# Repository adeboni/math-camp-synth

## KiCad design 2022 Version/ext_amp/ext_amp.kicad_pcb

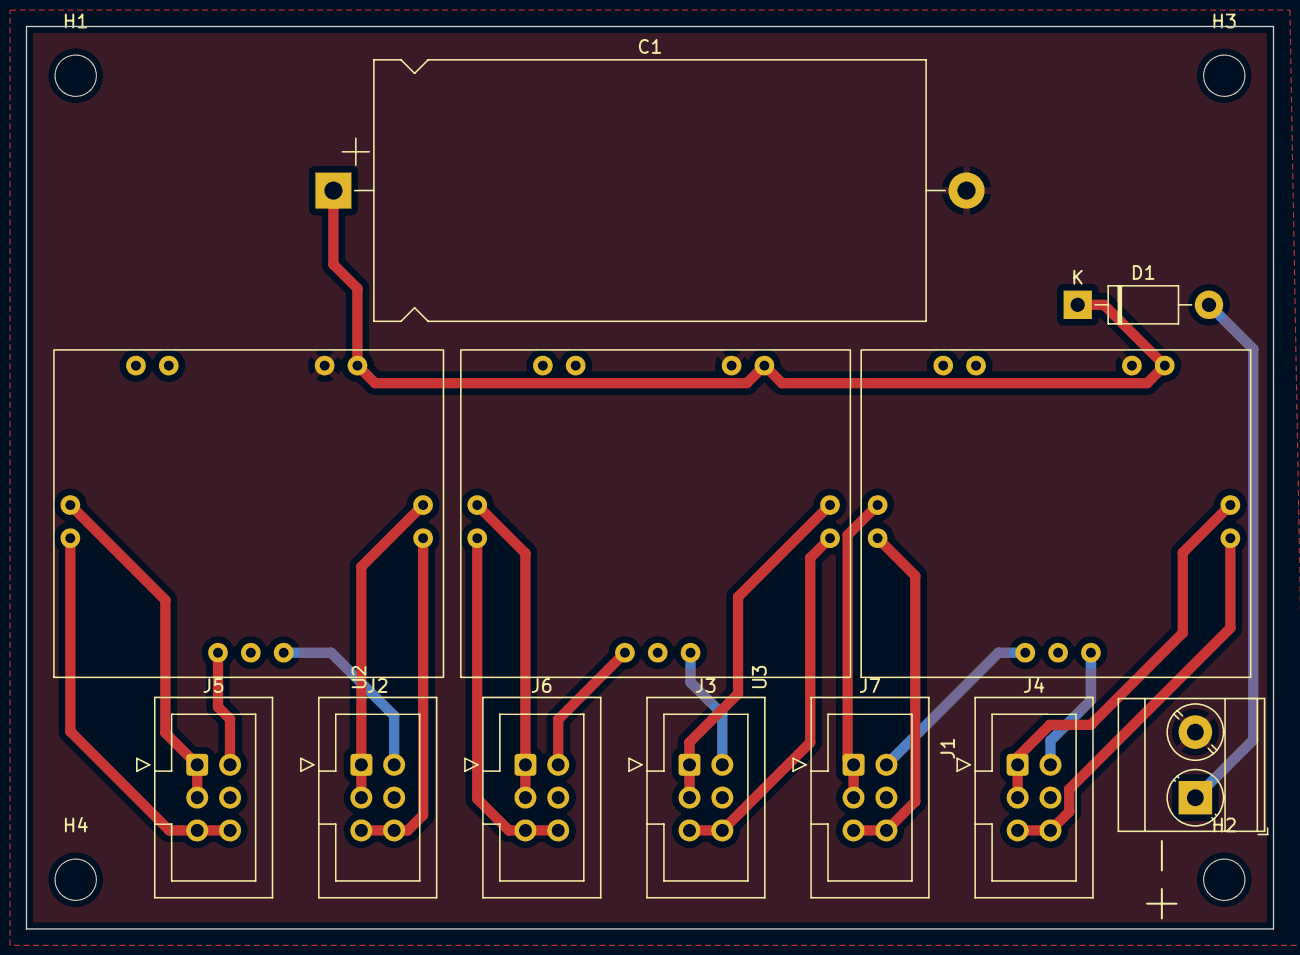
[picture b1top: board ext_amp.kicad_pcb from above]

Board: 2 copper layers, 96.5 x 69.9 mm, 16 parts (0 on the bottom side), 22 nets.

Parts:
C1: 4700u; CP_Axial_L42.5mm_D20.0mm_P49.00mm_Horizontal
D1: 1N4007; D_DO-41_SOD81_P10.16mm_Horizontal
H1, H2, H3, H4: MountingHole; MountingHole_3.2mm_M3
J1: Screw_Terminal_01x02; TerminalBlock_Phoenix_MKDS-3-2-5.08_1x02_P5.08mm_Horizontal
J2, J3, J4, J5, J6, J7: Conn_02x03_Odd_Even; IDC-Header_2x03_P2.54mm_Vertical
U1, U2, U3: PAM8610_Module

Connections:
+12V: C1.1, D1.1 (K), U1.2 (PWR_12V), U2.2 (PWR_12V), U3.2 (PWR_12V)
GND: C1.2, J1.2, U1.1 (PWR_GND), U2.1 (PWR_GND), U3.1 (PWR_GND)
IN1+: J2.2, U1.7 (L_IN)
IN2+: J5.2, U1.5 (R_IN)
IN3+: J3.2, U2.7 (L_IN)
IN4+: J6.2, U2.5 (R_IN)
IN5+: J4.2, U3.7 (L_IN)
IN6+: J7.2, U3.5 (R_IN)
IN-: J2.4, J3.4, J4.4, J5.4, J6.4, J7.4, U1.6 (GND_IN), U2.6 (GND_IN), U3.6 (GND_IN)
unnamed: D1.2 (A), J1.1
OUT1+: J2.1, J2.3, U1.11 (L+)
OUT1-: J2.5, J2.6, U1.10 (L-)
OUT2+: J5.1, J5.3, U1.9 (R+)
OUT2-: J5.5, J5.6, U1.8 (R-)
OUT3+: J3.1, J3.3, U2.11 (L+)
OUT3-: J3.5, J3.6, U2.10 (L-)
OUT4+: J6.1, J6.3, U2.9 (R+)
OUT4-: J6.5, J6.6, U2.8 (R-)
OUT5+: J4.1, J4.3, U3.11 (L+)
OUT5-: J4.5, J4.6, U3.10 (L-)
OUT6+: J7.1, J7.3, U3.9 (R+)
OUT6-: J7.5, J7.6, U3.8 (R-)

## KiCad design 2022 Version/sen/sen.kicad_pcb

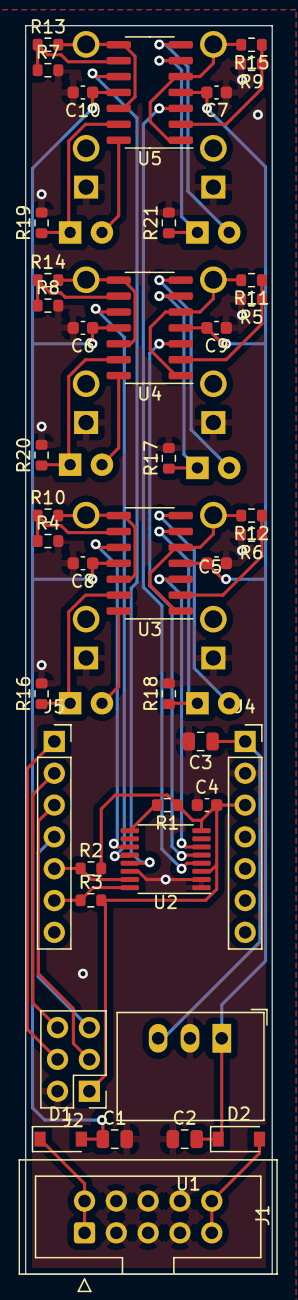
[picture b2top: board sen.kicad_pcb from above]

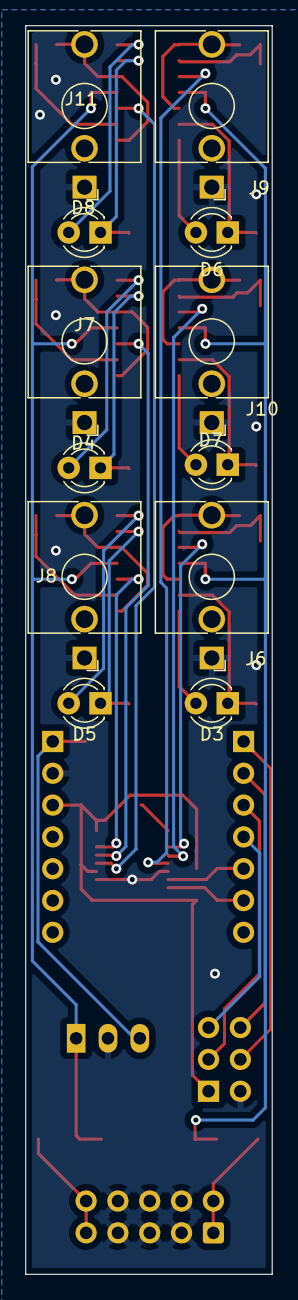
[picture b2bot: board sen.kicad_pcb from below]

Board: 2 copper layers, 19.7 x 99.7 mm, 54 parts (12 on the bottom side), 44 nets.

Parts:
C1, C2, C3: 22u; C_0805_2012Metric
C4, C5, C6, C7, C8, C9, C10: 100n; C_0603_1608Metric
D1, D2: 1N5819; D_SOD-123
D3, D4, D5, D6, D7, D8: LED; LED_D3.0mm_FlatTop
J1: Conn_02x05_Odd_Even; IDC-Header_2x05_P2.54mm_Vertical
J2: Conn_02x03_Odd_Even; PinHeader_2x03_P2.54mm_Vertical
J4, J5: Conn_01x07; PinSocket_1x07_P2.54mm_Vertical
J6, J7, J8, J9, J10, J11: AudioJack2_SwitchT; Jack_3.5mm_QingPu_WQP-PJ398SM_Vertical_CircularHoles
R1, R2, R3, R10, R11, R12, R13, R14, R15: 10k; R_0603_1608Metric
R4, R5, R6, R7, R8, R9: 4.7k; R_0603_1608Metric
R16, R17, R18, R19, R20, R21: 1k; R_0603_1608Metric
U1: R-78C3.3-1.0; Converter_DCDC_RECOM_R-78E-0.5_THT
U2: DAC7578xPW; TSSOP-16_4.4x5mm_P0.65mm
U3, U4, U5: TL074; SOIC-14_3.9x8.7mm_P1.27mm

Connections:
+3V3: C4.2, J2.1, J4.3, R1.1, R2.2, R3.2, U2.3 (AVDD), U2.8 (VREFIN)
+5V: C3.1, J4.1, U1.3 (OUT)
+12V: C2.2, C5.2, C7.2, C9.2, D2.1 (K), U1.1 (IN), U3.4 (V+), U4.4 (V+), U5.4 (V+)
-12V: C1.1, C6.1, C8.1, C10.1, D1.2 (A), U3.11 (V-), U4.11 (V-), U5.11 (V-)
A0: J2.4, J5.1
A1: J2.6, J5.2
A2: J2.3, J5.3
A3: J2.5, J5.4
GND: C1.2, C2.1, C3.2, C4.1, C5.1, C6.2, C7.1, C8.2, C9.1, C10.2, J1.3, J1.4, J1.5, J1.6, J1.7, J1.8, J2.2, J4.2, J6.S, J7.S, J8.S, J9.S, J10.S, J11.S, R4.2, R5.2, R6.2, R7.2, R8.2, R9.2, R16.2, R17.2, R18.2, R19.2, R20.2, R21.2, U1.2 (GND), U2.1 (~LDAC), U2.2 (ADDR0), U2.14 (GND)
unnamed: D1.1 (K), J1.1, J1.2
unnamed: D2.2 (A), J1.9, J1.10
unnamed: D3.1 (K), R16.1, U3.13 (-)
unnamed: D3.2 (A), U3.14
unnamed: D4.1 (K), R17.1, U4.6 (-)
unnamed: D4.2 (A), U4.7
unnamed: D5.1 (K), R18.1, U3.6 (-)
unnamed: D5.2 (A), U3.7
unnamed: D6.1 (K), R19.1, U5.13 (-)
unnamed: D6.2 (A), U5.14
unnamed: D7.1 (K), R20.1, U4.13 (-)
unnamed: D7.2 (A), U4.14
unnamed: D8.1 (K), R21.1, U5.6 (-)
unnamed: D8.2 (A), U5.7
unnamed: J6.T, R10.2, U3.8, U3.12 (+)
unnamed: J7.T, R11.2, U4.1, U4.5 (+)
unnamed: J8.T, R12.2, U3.1, U3.5 (+)
unnamed: J9.T, R13.2, U5.8, U5.12 (+)
unnamed: J10.T, R14.2, U4.8, U4.12 (+)
unnamed: J11.T, R15.2, U5.1, U5.5 (+)
unnamed: R1.2, U2.9 (~CLR)
unnamed: R4.1, R10.1, U3.9 (-)
unnamed: R5.1, R11.1, U4.2 (-)
unnamed: R6.1, R12.1, U3.2 (-)
unnamed: R7.1, R13.1, U5.9 (-)
unnamed: R8.1, R14.1, U4.9 (-)
unnamed: R9.1, R15.1, U5.2 (-)
unnamed: U2.4 (VOUTA), U5.3 (+)
unnamed: U2.5 (VOUTC), U4.3 (+)
unnamed: U2.6 (VOUTE), U3.3 (+)
unnamed: U2.11 (VOUTF), U3.10 (+)
unnamed: U2.12 (VOUTD), U4.10 (+)
unnamed: U2.13 (VOUTB), U5.10 (+)
SCL: J5.6, R3.1, U2.16 (SCL)
SDA: J5.5, R2.1, U2.15 (SDA)

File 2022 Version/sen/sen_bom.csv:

Comment,Designator,Footprint,LCSC Part Number
100n,"C7,C5,C10,C4,C6,C8,C9",C_0603_1608Metric,C14663
1k,"R19,R18,R20,R16,R17,R21",R_0603_1608Metric,C21190
10k,"R15,R3,R13,R11,R2,R12,R1,R14,R10",R_0603_1608Metric,C25804
22u,"C2,C1,C3",C_0805_2012Metric,C129303
TL074,"U4,U3,U5",SOIC-14_3.9x8.7mm_P1.27mm,C6963
DAC7578xPW,U2,TSSOP-16_4.4x5mm_P0.65mm,C1520855
4.7k,"R4,R7,R9,R6,R8,R5",R_0603_1608Metric,C23162
1N5819,"D1,D2",D_SOD-123,C963381

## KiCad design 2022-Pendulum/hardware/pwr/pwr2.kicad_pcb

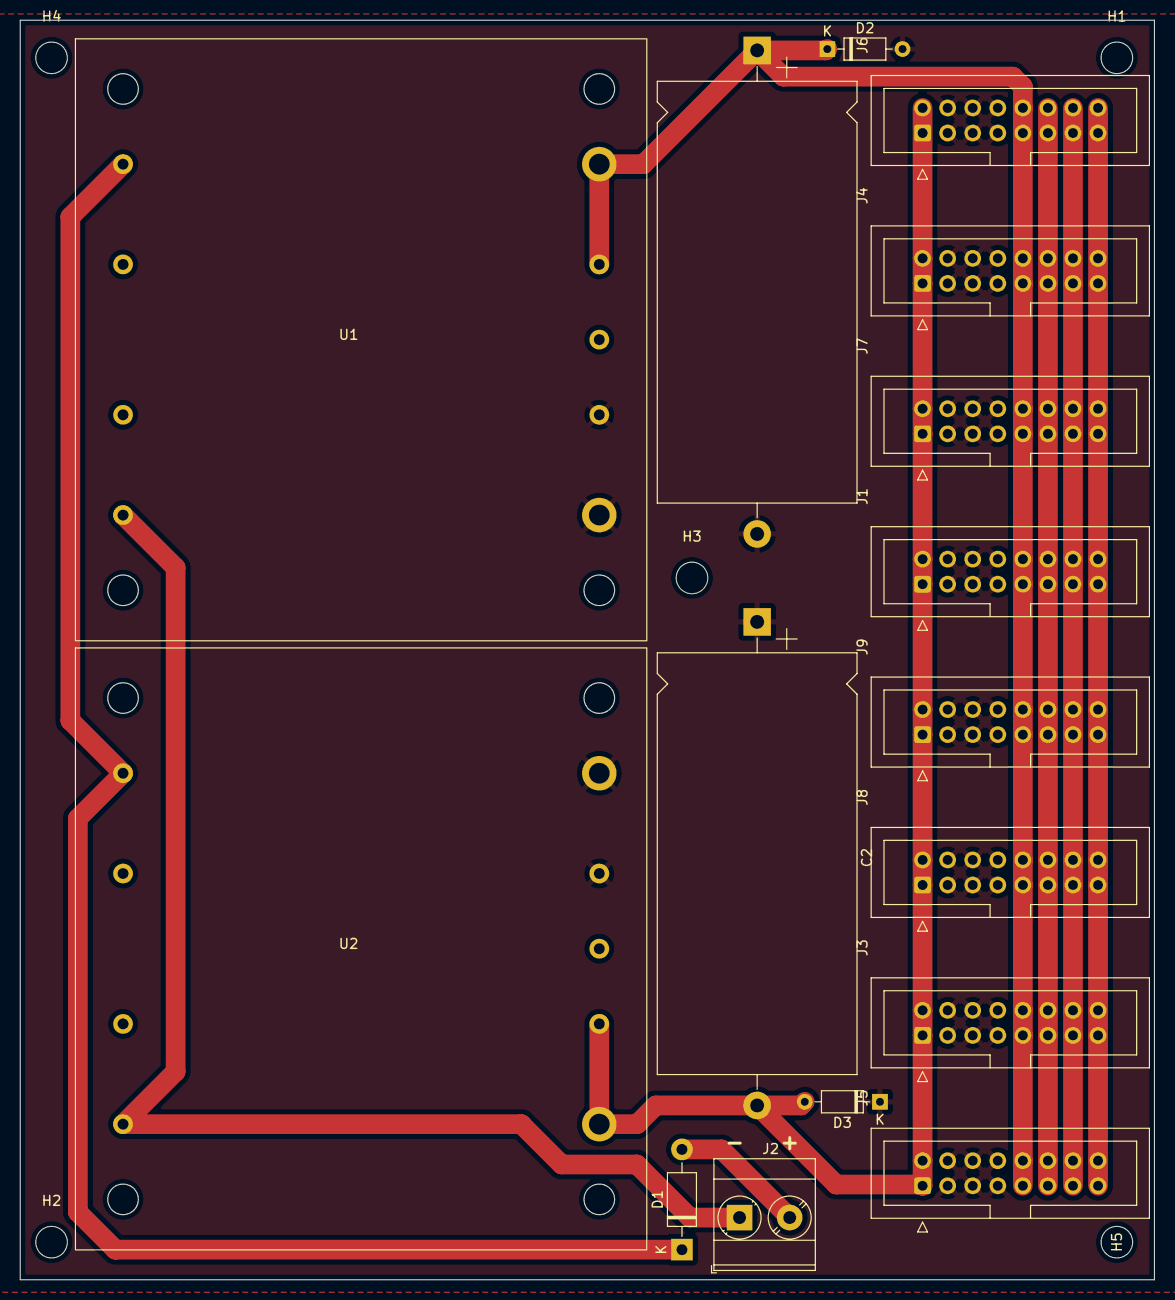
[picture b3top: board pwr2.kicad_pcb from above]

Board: 2 copper layers, 114.9 x 127.6 mm, 21 parts (0 on the bottom side), 9 nets.

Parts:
C1, C2: 4700u; CP_Axial_L42.5mm_D20.0mm_P49.00mm_Horizontal
D1: 1N4007; D_DO-41_SOD81_P10.16mm_Horizontal
D2, D3: 1N4148; D_DO-35_SOD27_P7.62mm_Horizontal
H1, H2, H3, H4, H5: MountingHole; MountingHole_3.2mm_M3
J1, J3, J4, J5, J6, J7, J8, J9: Conn_02x08_Odd_Even; IDC-Header_2x08_P2.54mm_Vertical
J2: Screw_Terminal_01x02; TerminalBlock_Phoenix_MKDS-3-2-5.08_1x02_P5.08mm_Horizontal
U1, U2: VHB75

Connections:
+12V: C1.1, D2.1 (K), J1.9, J1.10, J3.9, J3.10, J4.9, J4.10, J5.9, J5.10, J6.9, J6.10, J7.9, J7.10, J8.9, J8.10, J9.9, J9.10, U1.8 (+Sense), U1.9 (+Vout)
-12V: C2.2, D3.2 (A), J1.1, J1.2, J3.1, J3.2, J4.1, J4.2, J5.1, J5.2, J6.1, J6.2, J7.1, J7.2, J8.1, J8.2, J9.1, J9.2, U2.5 (-Vout), U2.6 (-Sense)
GND: C1.2, C2.1, D2.2 (A), D3.1 (K), J1.3, J1.4, J1.5, J1.6, J1.7, J1.8, J3.3, J3.4, J3.5, J3.6, J3.7, J3.8, J4.3, J4.4, J4.5, J4.6, J4.7, J4.8, J5.3, J5.4, J5.5, J5.6, J5.7, J5.8, J6.3, J6.4, J6.5, J6.6, J6.7, J6.8, J7.3, J7.4, J7.5, J7.6, J7.7, J7.8, J8.3, J8.4, J8.5, J8.6, J8.7, J8.8, J9.3, J9.4, J9.5, J9.6, J9.7, J9.8, U1.5 (-Vout), U1.6 (-Sense), U2.8 (+Sense), U2.9 (+Vout)
unnamed: D1.1 (K), U1.1 (+Vin), U2.1 (+Vin)
unnamed: D1.2 (A), J2.2
unnamed: J1.11, J1.12, J3.11, J3.12, J4.11, J4.12, J5.11, J5.12, J6.11, J6.12, J7.11, J7.12, J8.11, J8.12, J9.11, J9.12
unnamed: J1.13, J1.14, J3.13, J3.14, J4.13, J4.14, J5.13, J5.14, J6.13, J6.14, J7.13, J7.14, J8.13, J8.14, J9.13, J9.14
unnamed: J1.15, J1.16, J3.15, J3.16, J4.15, J4.16, J5.15, J5.16, J6.15, J6.16, J7.15, J7.16, J8.15, J8.16, J9.15, J9.16
unnamed: J2.1, U1.4 (-Vin), U2.4 (-Vin)

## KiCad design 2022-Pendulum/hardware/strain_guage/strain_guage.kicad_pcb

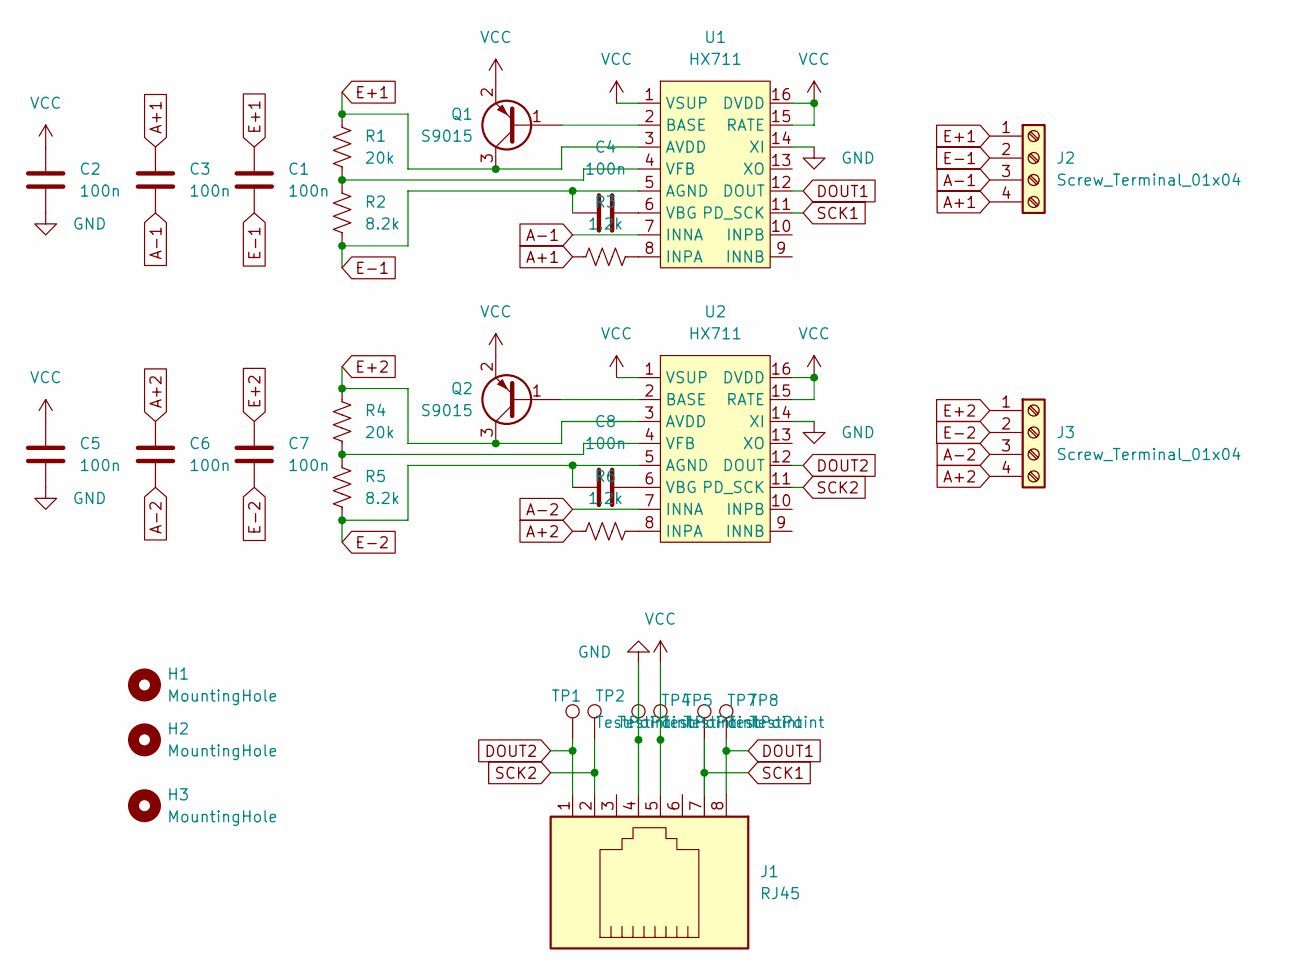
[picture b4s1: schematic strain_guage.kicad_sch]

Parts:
C1, C2, C3, C4, C5, C6, C7, C8: 100n; C_0603_1608Metric
H1, H2, H3: MountingHole; MountingHole_3.2mm_M3
J1: RJ45; RJ45_OST_PJ012-8P8CX_Vertical
J2, J3: Screw_Terminal_01x04; TerminalBlock_bornier-4_P5.08mm
Q1, Q2: S9015; SOT-23
R1, R4: 20k; R_0603_1608Metric
R2, R5: 8.2k; R_0603_1608Metric
R3, R6: 1.2k; R_0603_1608Metric
TP1, TP2, TP4, TP5, TP7, TP8: TestPoint; TestPoint_WireHole
U1, U2: HX711; SOIC-16_3.9x9.9mm_P1.27mm

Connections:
A+1: C3.1, J2.4, R3.1
A+2: C6.1, J3.4, R6.1
A-1: C3.2, J2.3, U1.7 (INNA)
A-2: C6.2, J3.3, U2.7 (INNA)
DOUT1: J1.8, TP8.1, U1.12 (DOUT)
DOUT2: J1.1, TP1.1, U2.12 (DOUT)
E+1: C1.1, J2.1, Q1.3 (C), R1.1, U1.3 (AVDD)
E+2: C7.1, J3.1, Q2.3 (C), R4.1, U2.3 (AVDD)
E-1: C1.2, C4.1, J2.2, R2.2, U1.5 (AGND)
E-2: C7.2, C8.1, J3.2, R5.2, U2.5 (AGND)
GND: C2.2, C5.2, J1.4, TP4.1, U1.14 (XI), U2.14 (XI)
unnamed: C8.2, U2.6 (VBG)
unnamed: Q2.1 (B), U2.2 (BASE)
unnamed: R4.2, R5.1, U2.4 (VFB)
unnamed: R6.2, U2.8 (INPA)
unnamed: Q1.1 (B), U1.2 (BASE)
unnamed: R1.2, R2.1, U1.4 (VFB)
unnamed: C4.2, U1.6 (VBG)
unnamed: R3.2, U1.8 (INPA)
SCK1: J1.7, TP7.1, U1.11 (PD_SCK)
SCK2: J1.2, TP2.1, U2.11 (PD_SCK)
VCC: C2.1, C5.1, J1.5, Q1.2 (E), Q2.2 (E), TP5.1, U1.1 (VSUP), U1.15 (RATE), U1.16 (DVDD), U2.1 (VSUP), U2.15 (RATE), U2.16 (DVDD)

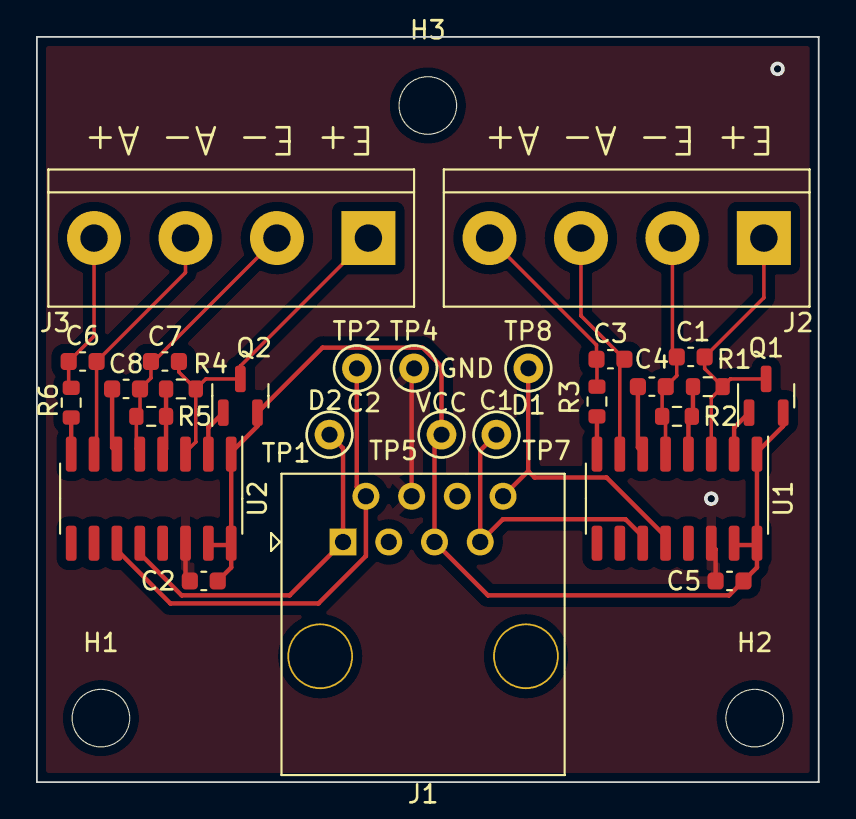
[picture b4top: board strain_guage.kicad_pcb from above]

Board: 2 copper layers, 43.4 x 41.4 mm, 30 parts (0 on the bottom side), 22 nets.

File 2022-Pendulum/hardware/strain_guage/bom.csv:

Comment,Designator,Footprint,LCSC Part Number
HX711,"U2,U1",SOIC-16_3.9x9.9mm_P1.27mm,C43656
100n,"C5,C2,C6,C1,C3,C8,C7,C4",C_0603_1608Metric,C14663
1.2k,"R6,R3",R_0603_1608Metric,C22765
8.2k,"R5,R2",R_0603_1608Metric,C25981
S9015,"Q1,Q2",SOT-23,C2149
20k,"R1,R4",R_0603_1608Metric,C4184

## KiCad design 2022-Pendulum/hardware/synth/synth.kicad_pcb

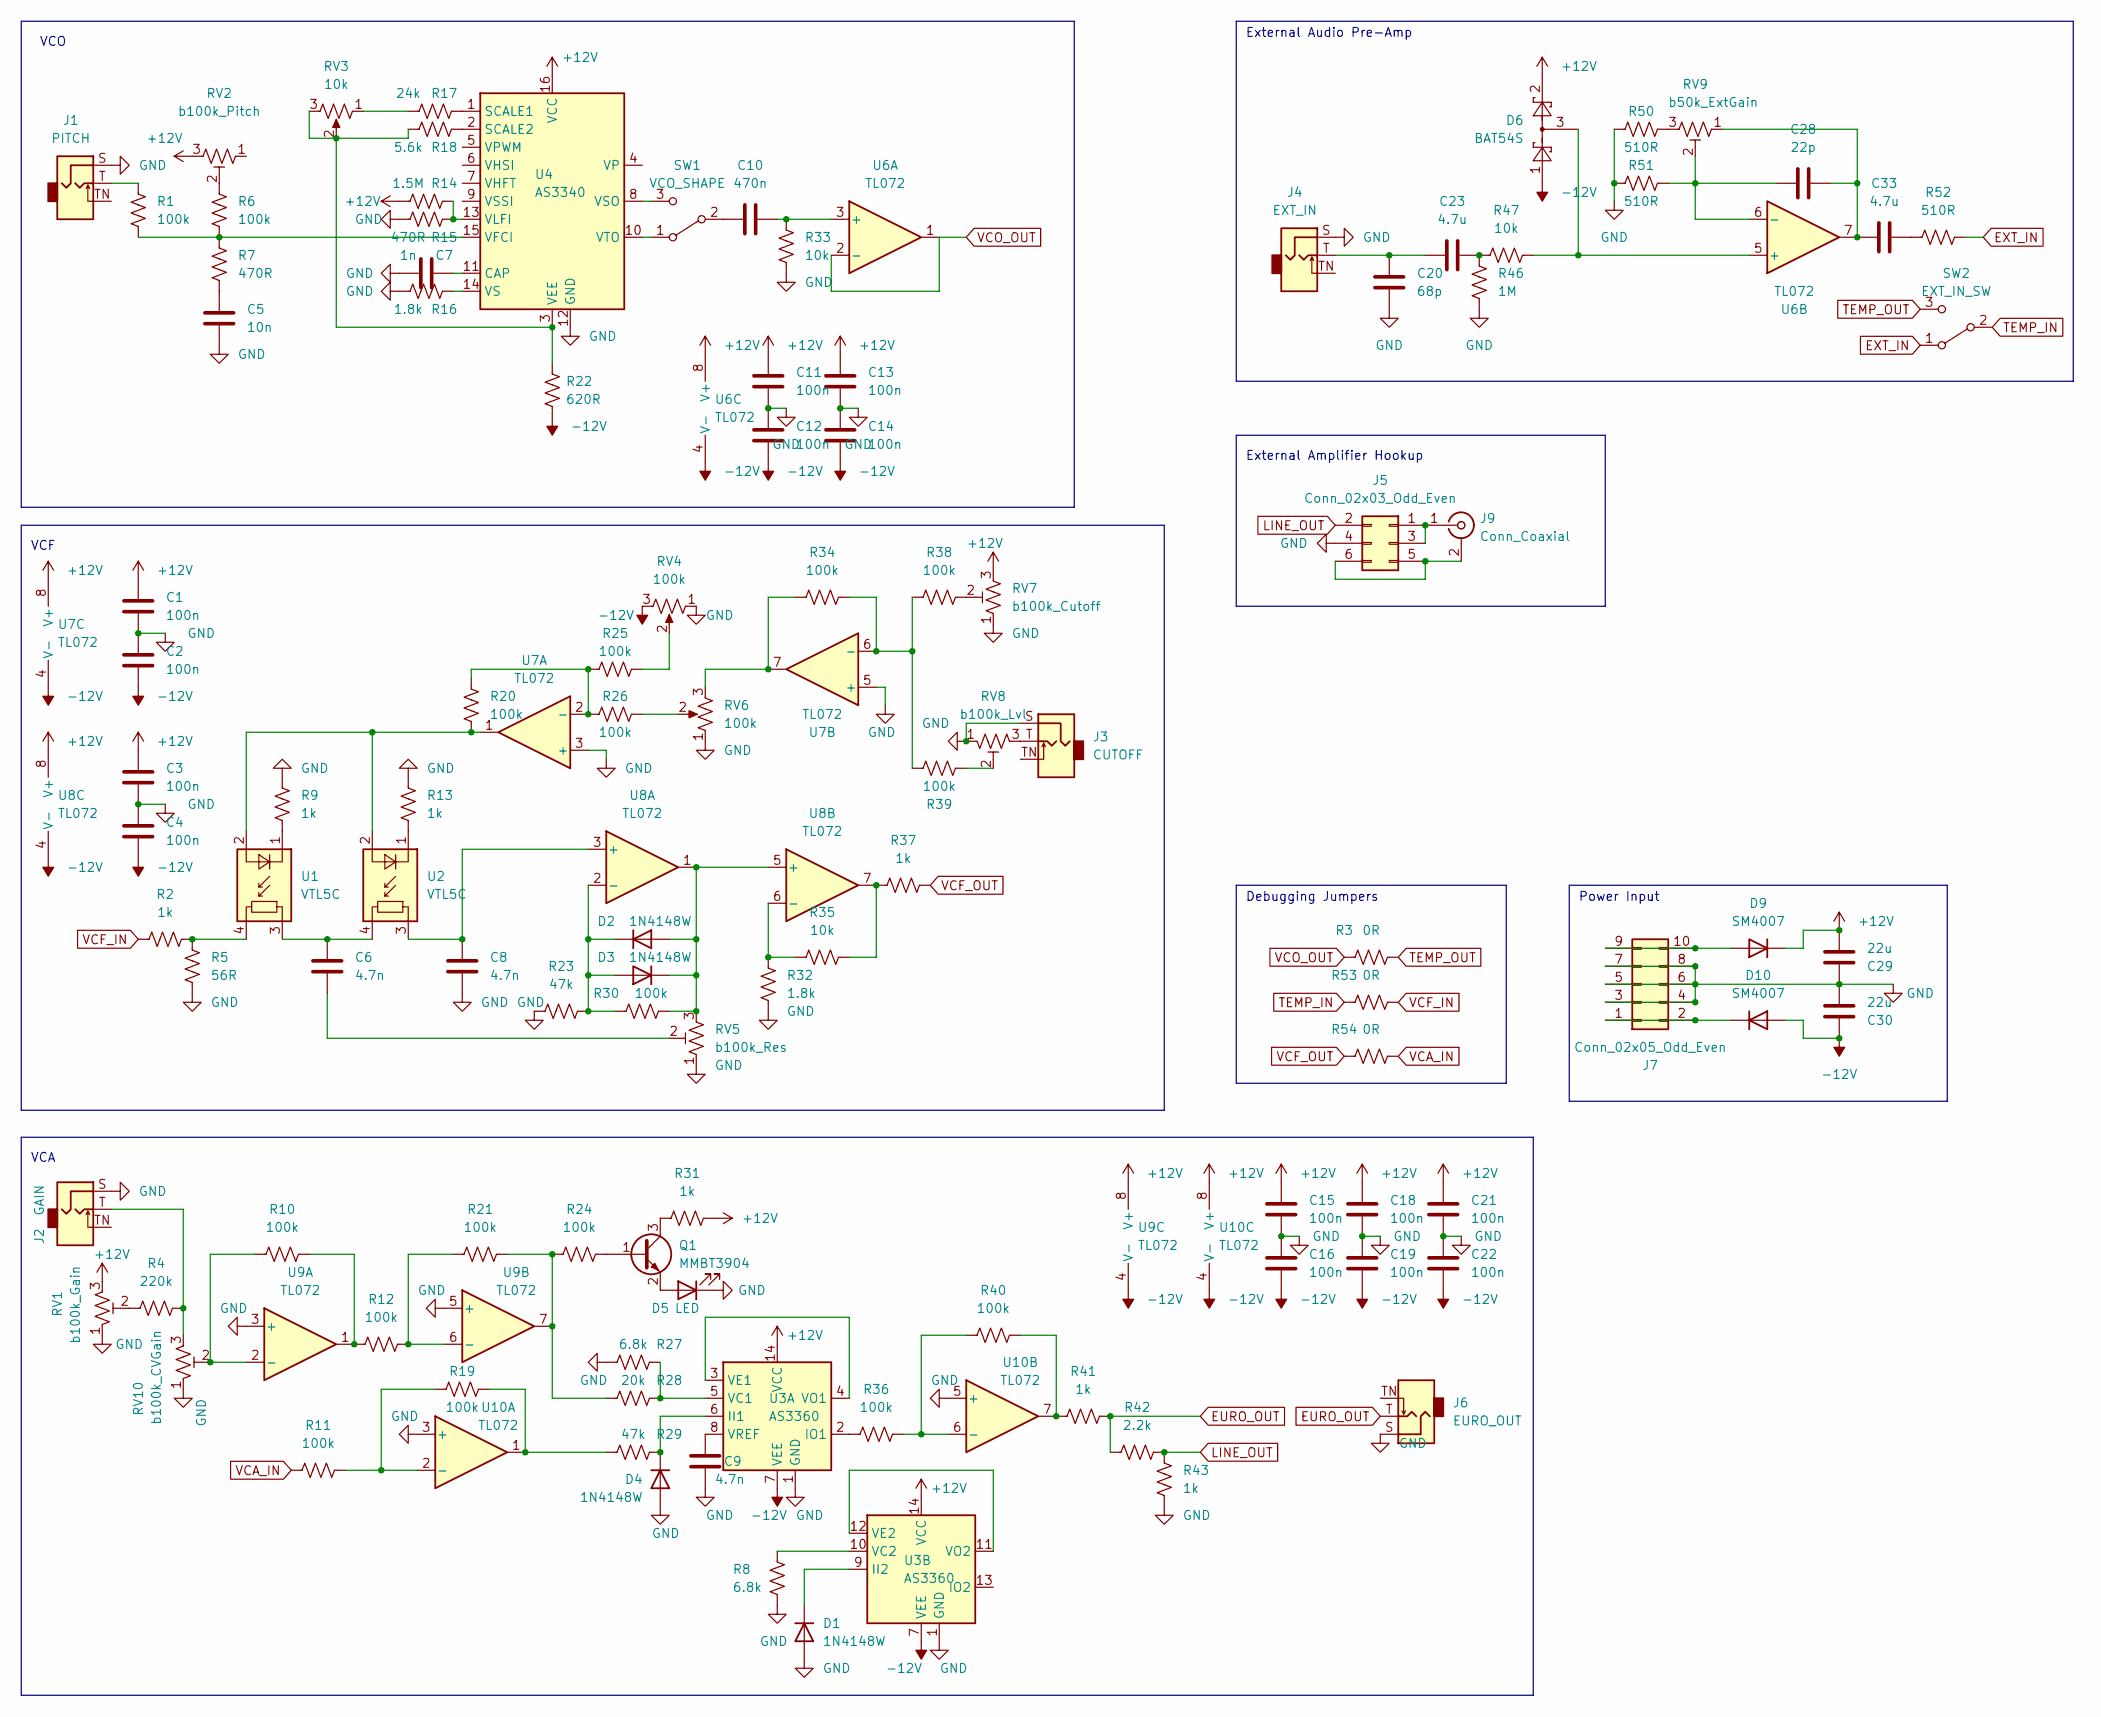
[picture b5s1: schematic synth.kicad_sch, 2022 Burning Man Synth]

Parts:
C1, C2, C3, C4, C11, C12, C13, C14, C15, C16, C18, C19, C21, C22: 100n; C_0603_1608Metric
C5: 10n; C_0603_1608Metric
C6, C8, C9: 4.7n; C_0603_1608Metric
C7: 1n; C_0603_1608Metric
C10: 470n; C_0603_1608Metric
C20: 68p; C_0603_1608Metric
C23, C33: 4.7u; C_0603_1608Metric
C28: 22p; C_0603_1608Metric
C29, C30: 22u; C_0805_2012Metric
D1, D2, D3, D4: 1N4148W; D_SOD-123
D5: LED; LED_D3.0mm
D6: BAT54S; SOT-23
D9, D10: SM4007; D_SOD-123
J1: PITCH; Jack_3.5mm_QingPu_WQP-PJ398SM_Vertical_CircularHoles
J2: GAIN; Jack_3.5mm_QingPu_WQP-PJ398SM_Vertical_CircularHoles
J3: CUTOFF; Jack_3.5mm_QingPu_WQP-PJ398SM_Vertical_CircularHoles
J4: EXT_IN; Jack_3.5mm_QingPu_WQP-PJ398SM_Vertical_CircularHoles
J5: Conn_02x03_Odd_Even; IDC-Header_2x03_P2.54mm_Vertical
J6: EURO_OUT; Jack_3.5mm_QingPu_WQP-PJ398SM_Vertical_CircularHoles
J7: Conn_02x05_Odd_Even; IDC-Header_2x05_P2.54mm_Vertical
J9: Conn_Coaxial; RCA
Q1: MMBT3904; SOT-23
R1, R6, R10, R11, R12, R19, R20, R21, R24, R25, R26, R30, R34, R36, R38, R39, R40: 100k; R_0603_1608Metric
R2, R9, R13, R31, R37, R41, R43: 1k; R_0603_1608Metric
R3, R53, R54: 0R; R_0603_1608Metric
R4: 220k; R_0603_1608Metric
R5: 56R; R_0603_1608Metric
R7, R15: 470R; R_0603_1608Metric
R8, R27: 6.8k; R_0603_1608Metric
R14: 1.5M; R_0603_1608Metric
R16, R32: 1.8k; R_0603_1608Metric
R17: 24k; R_0603_1608Metric
R18: 5.6k; R_0603_1608Metric
R22: 620R; R_0603_1608Metric
R23, R29: 47k; R_0603_1608Metric
R28: 20k; R_0603_1608Metric
R33, R35, R47: 10k; R_0603_1608Metric
R42: 2.2k; R_0603_1608Metric
R46: 1M; R_0603_1608Metric
R50, R51, R52: 510R; R_0603_1608Metric
RV1: b100k_Gain; Potentiometer_Alpha_RD901F-40-00D_Single_Vertical
RV2: b100k_Pitch; Potentiometer_Alpha_RD901F-40-00D_Single_Vertical
RV3: 10k; Potentiometer_Bourns_3314G_Vertical
RV4, RV6: 100k; Potentiometer_Bourns_3314G_Vertical
RV5: b100k_Res; Potentiometer_Alpha_RD901F-40-00D_Single_Vertical
RV7: b100k_Cutoff; Potentiometer_Alpha_RD901F-40-00D_Single_Vertical
RV8: b100k_Lvl; Potentiometer_Alpha_RD901F-40-00D_Single_Vertical
RV9: b50k_ExtGain; Potentiometer_Alpha_RD901F-40-00D_Single_Vertical
RV10: b100k_CVGain; Potentiometer_Alpha_RD901F-40-00D_Single_Vertical
SW1: VCO_SHAPE; Switch_Toggle_SPDT_Mini_SolderLug
SW2: EXT_IN_SW; Switch_Toggle_SPDT_Mini_SolderLug
U1, U2: VTL5C; PerkinElmer_VTL5C
U3: AS3360; DIP-14_W7.62mm
U4: AS3340; DIP-16_W7.62mm
U6, U7, U8, U9, U10: TL072; SOIC-8_3.9x4.9mm_P1.27mm

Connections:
+12V: C1.2, C3.2, C11.1, C13.1, C15.2, C18.2, C21.2, C29.2, D6.2, D9.1 (K), R14.1, R31.2, RV1.3, RV2.3, RV7.3, U3.14 (VCC), U4.16 (VCC), U6.8 (V+), U7.8 (V+), U8.8 (V+), U9.8 (V+), U10.8 (V+); also elsewhere on the board
-12V: C2.1, C4.1, C12.2, C14.2, C16.1, C19.1, C22.1, C30.1, D6.1, D10.2 (A), R22.1, RV4.3, U3.7 (VEE), U6.4 (V-), U7.4 (V-), U8.4 (V-), U9.4 (V-), U10.4 (V-)
EURO_OUT: J6.T, R41.2, R42.2
EXT_IN: R52.1, SW2.1 (A)
GND: C1.1, C2.2, C3.1, C4.2, C5.2, C7.1, C8.1, C9.1, C11.2, C12.1, C13.2, C14.1, C15.1, C16.2, C18.1, C19.2, C20.1, C21.1, C22.2, C29.1, C30.2, D1.2 (A), D4.2 (A), D5.1 (K), J1.S, J2.S, J3.S, J4.S, J5.4, J6.S, J7.3, J7.4, J7.5, J7.6, J7.7, J7.8, R5.1, R8.1, R9.2, R13.2, R15.1, R16.1, R23.2, R27.1, R32.2, R33.1, R43.1, R46.1, R50.2, R51.2, RV1.1, RV4.1, RV5.1, RV6.1, RV7.1, RV8.1, RV10.1, U3.1 (GND), U4.12 (GND), U7.3 (+), U7.5 (+), U9.3 (+), U9.5 (+), U10.3 (+), U10.5 (+); also elsewhere on the board
LINE_OUT: J5.2, R42.1, R43.2
unnamed: C5.1, R7.1
unnamed 7: C6.1, RV5.2; also elsewhere on the board
unnamed: C6.2, U1.3, U2.4
unnamed: C7.2, U4.11 (CAP)
unnamed: C8.2, U2.3, U8.3 (+)
unnamed: C9.2, U3.8 (VREF)
unnamed: C10.1, SW1.2 (B)
unnamed: C10.2, R33.2, U6.3 (+)
unnamed: C20.2, C23.2, J4.T
unnamed: C23.1, R46.2, R47.2
unnamed 16: C28.1, R51.1, RV9.2, U6.6 (-); also elsewhere on the board
unnamed 17: C28.2, C33.1, RV9.1, U6.7; also elsewhere on the board
unnamed: C33.2, R52.2
unnamed: D1.1 (K), U3.9 (II2)
unnamed: D2.1 (K), D3.2 (A), R23.1, R30.2, U8.2 (-)
unnamed 21: D2.2 (A), D3.1 (K), R30.1, RV5.3, U8.1, U8.5 (+); also elsewhere on the board
unnamed: D4.1 (K), R29.2, U3.6 (II1)
unnamed: D5.2 (A), Q1.2 (E)
unnamed: D6.3, R47.1, U6.5 (+)
unnamed: D9.2 (A), J7.9, J7.10
unnamed: D10.1 (K), J7.1, J7.2
unnamed: J1.T, R1.2
unnamed: J2.T, R4.2, RV10.3
unnamed 29: J3.T, RV8.3; also elsewhere on the board
unnamed: J5.1, J5.3, J9.1 (In)
unnamed: J5.5, J5.6, J9.2 (Ext)
unnamed: Q1.1 (B), R24.2
unnamed: Q1.3 (C), R31.1
unnamed: R1.1, R6.1, R7.2, U4.15 (VFCI)
unnamed: R2.2, R5.2, U1.4
unnamed 36: R4.1, RV1.2; also elsewhere on the board
unnamed 37: R6.2, RV2.2; also elsewhere on the board
unnamed: R8.2, U3.10 (VC2)
unnamed: R9.1, U1.1 (-)
unnamed: R10.1, RV10.2, U9.2 (-)
unnamed: R10.2, R12.1, U9.1
unnamed: R11.2, R19.1, U10.2 (-)
unnamed: R12.2, R21.1, U9.6 (-)
unnamed: R13.1, U2.1 (-)
unnamed: R14.2, R15.2, U4.13 (VLFI)
unnamed: R16.2, U4.14 (VS)
unnamed: R17.1, RV3.1
unnamed: R17.2, U4.1 (SCALE1)
unnamed: R18.1, R22.2, RV3.2, RV3.3, U4.3 (VEE)
unnamed: R18.2, U4.2 (SCALE2)
unnamed: R19.2, R29.1, U10.1
unnamed: R20.1, U1.2 (+), U2.2 (+), U7.1
unnamed: R20.2, R25.2, R26.2, U7.2 (-)
unnamed: R21.2, R24.1, R28.1, U9.7
unnamed: R25.1, RV4.2
unnamed: R26.1, RV6.2
unnamed: R27.2, R28.2, U3.5 (VC1)
unnamed: R32.1, R35.2, U8.6 (-)
unnamed: R34.1, R38.2, R39.2, U7.6 (-)
unnamed: R34.2, RV6.3, U7.7
unnamed: R35.1, R37.2, U8.7
unnamed: R36.1, U3.2 (IO1)
unnamed: R36.2, R40.1, U10.6 (-)
unnamed 64: R38.1, RV7.2; also elsewhere on the board
unnamed 65: R39.1, RV8.2; also elsewhere on the board
unnamed: R40.2, R41.1, U10.7
unnamed 67: R50.1, RV9.3; also elsewhere on the board
unnamed: SW1.1 (A), U4.10 (VTO)
unnamed: SW1.3 (C), U4.8 (VSO)
unnamed: U3.3 (VE1), U3.4 (VO1)
unnamed: U3.11 (VO2), U3.12 (VE2)
TEMP_IN: R53.1, SW2.2 (B)
TEMP_OUT: R3.2, SW2.3 (C)
VCA_IN: R11.1, R54.2
VCF_IN: R2.1, R53.2
VCF_OUT: R37.1, R54.1
VCO_OUT: R3.1, U6.1, U6.2 (-)

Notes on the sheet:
VCF
VCA
Debugging Jumpers
VCO
Power Input
External Amplifier Hookup
External Audio Pre-Amp

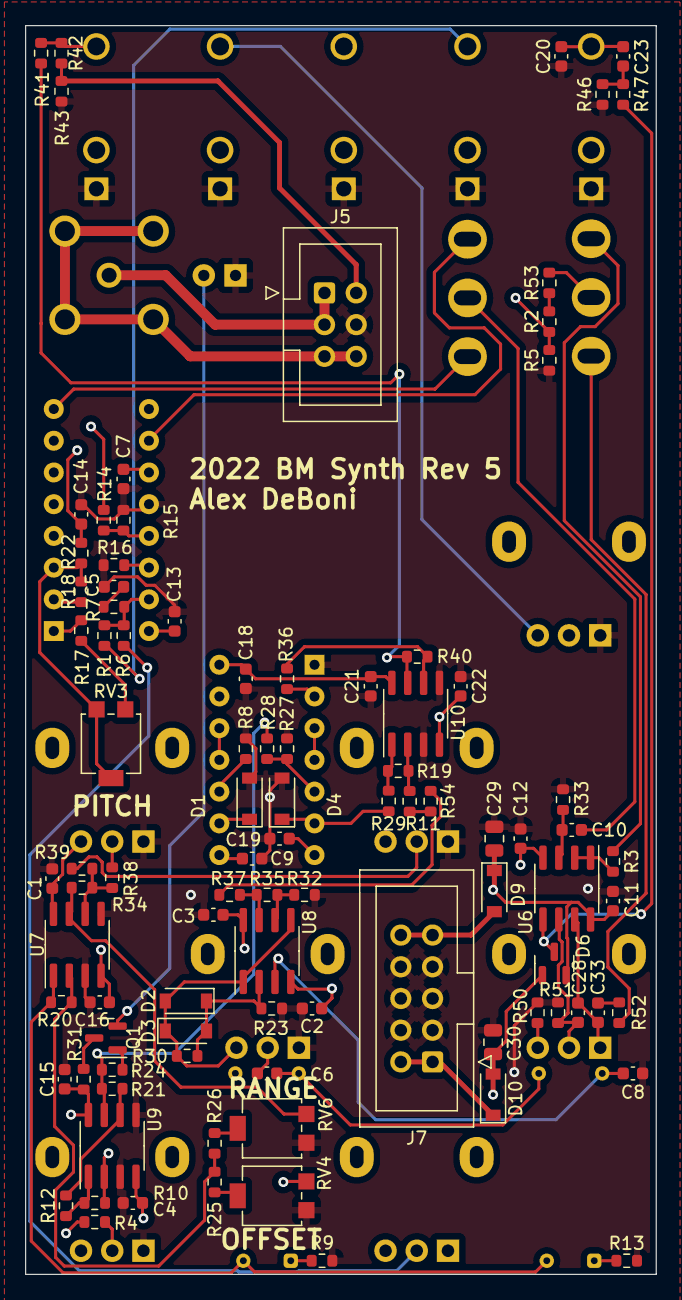
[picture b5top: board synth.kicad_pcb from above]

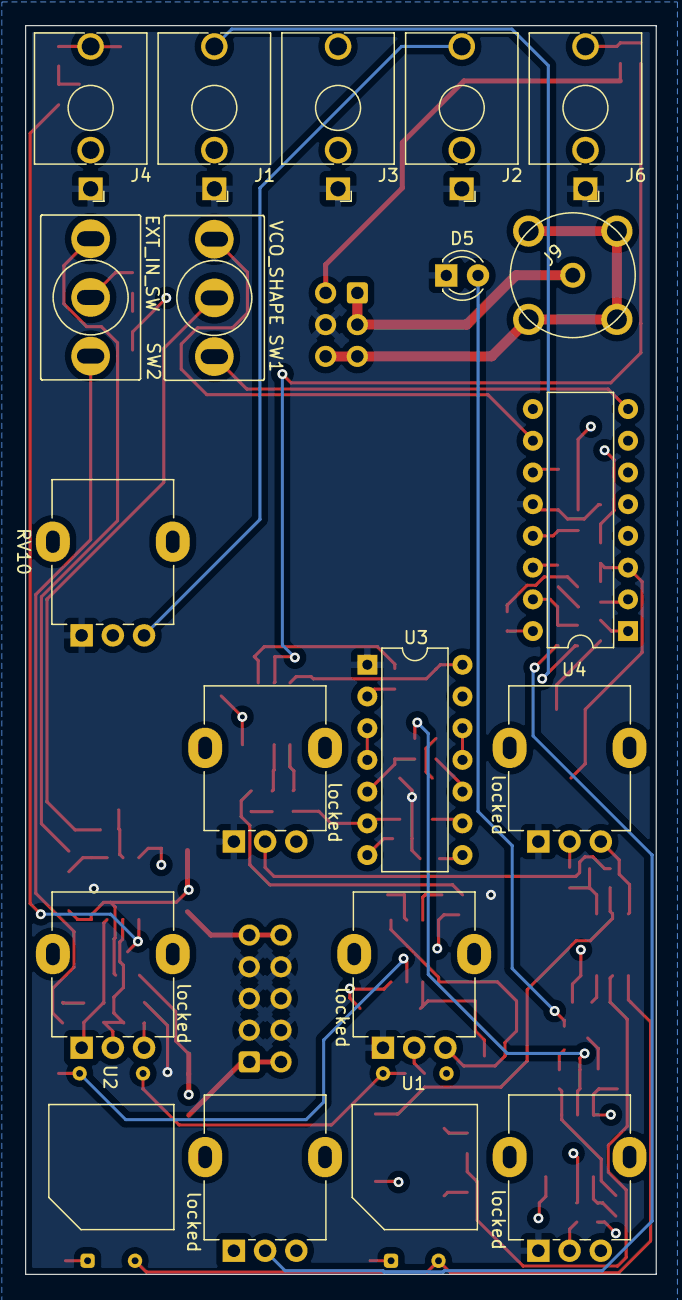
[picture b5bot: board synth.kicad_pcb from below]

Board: 4 copper layers, 50.5 x 100.0 mm, 114 parts (20 on the bottom side), 78 nets.

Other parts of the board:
locked: b50k_ExtGain; Potentiometer_Alpha_RD901F-40-00D_Single_Vertical
locked#2: b100k_Res; Potentiometer_Alpha_RD901F-40-00D_Single_Vertical
locked#3: b100k_Gain; Potentiometer_Alpha_RD901F-40-00D_Single_Vertical
locked#4: b100k_Lvl; Potentiometer_Alpha_RD901F-40-00D_Single_Vertical
locked#5: b100k_Pitch; Potentiometer_Alpha_RD901F-40-00D_Single_Vertical
locked#6: b100k_Cutoff; Potentiometer_Alpha_RD901F-40-00D_Single_Vertical

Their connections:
+12V: locked#3.3, locked#5.3, locked#6.3; also elsewhere on the board
GND: locked#2.1, locked#3.1, locked#4.1, locked#6.1; also elsewhere on the board
unnamed 7: locked#2.2; also elsewhere on the board
unnamed 16: locked.2; also elsewhere on the board
unnamed 17: locked.1; also elsewhere on the board
unnamed 21: locked#2.3; also elsewhere on the board
unnamed 29: locked#4.3; also elsewhere on the board
unnamed 36: locked#3.2; also elsewhere on the board
unnamed 37: locked#5.2; also elsewhere on the board
unnamed 64: locked#6.2; also elsewhere on the board
unnamed 65: locked#4.2; also elsewhere on the board
unnamed 67: locked.3; also elsewhere on the board
